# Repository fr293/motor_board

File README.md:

# stepper motor control board

This motor control board is designed to work with the [Open Flexure microscope](https://github.com/rwb27/openflexure_microscope) and connect to a Raspberry Pi.  It is based around three parallel ATTiny 841 microcontrollers running the Arduino Firmware through SpenceKonde's [ATTinyCore](https://github.com/SpenceKonde/ATTinyCore). 

Each ATTiny 841 controls a ULN2003 Darlington transistor array operating at 5V, running a 28BYJ-48 stepper motor with a 64:1 gear ratio.

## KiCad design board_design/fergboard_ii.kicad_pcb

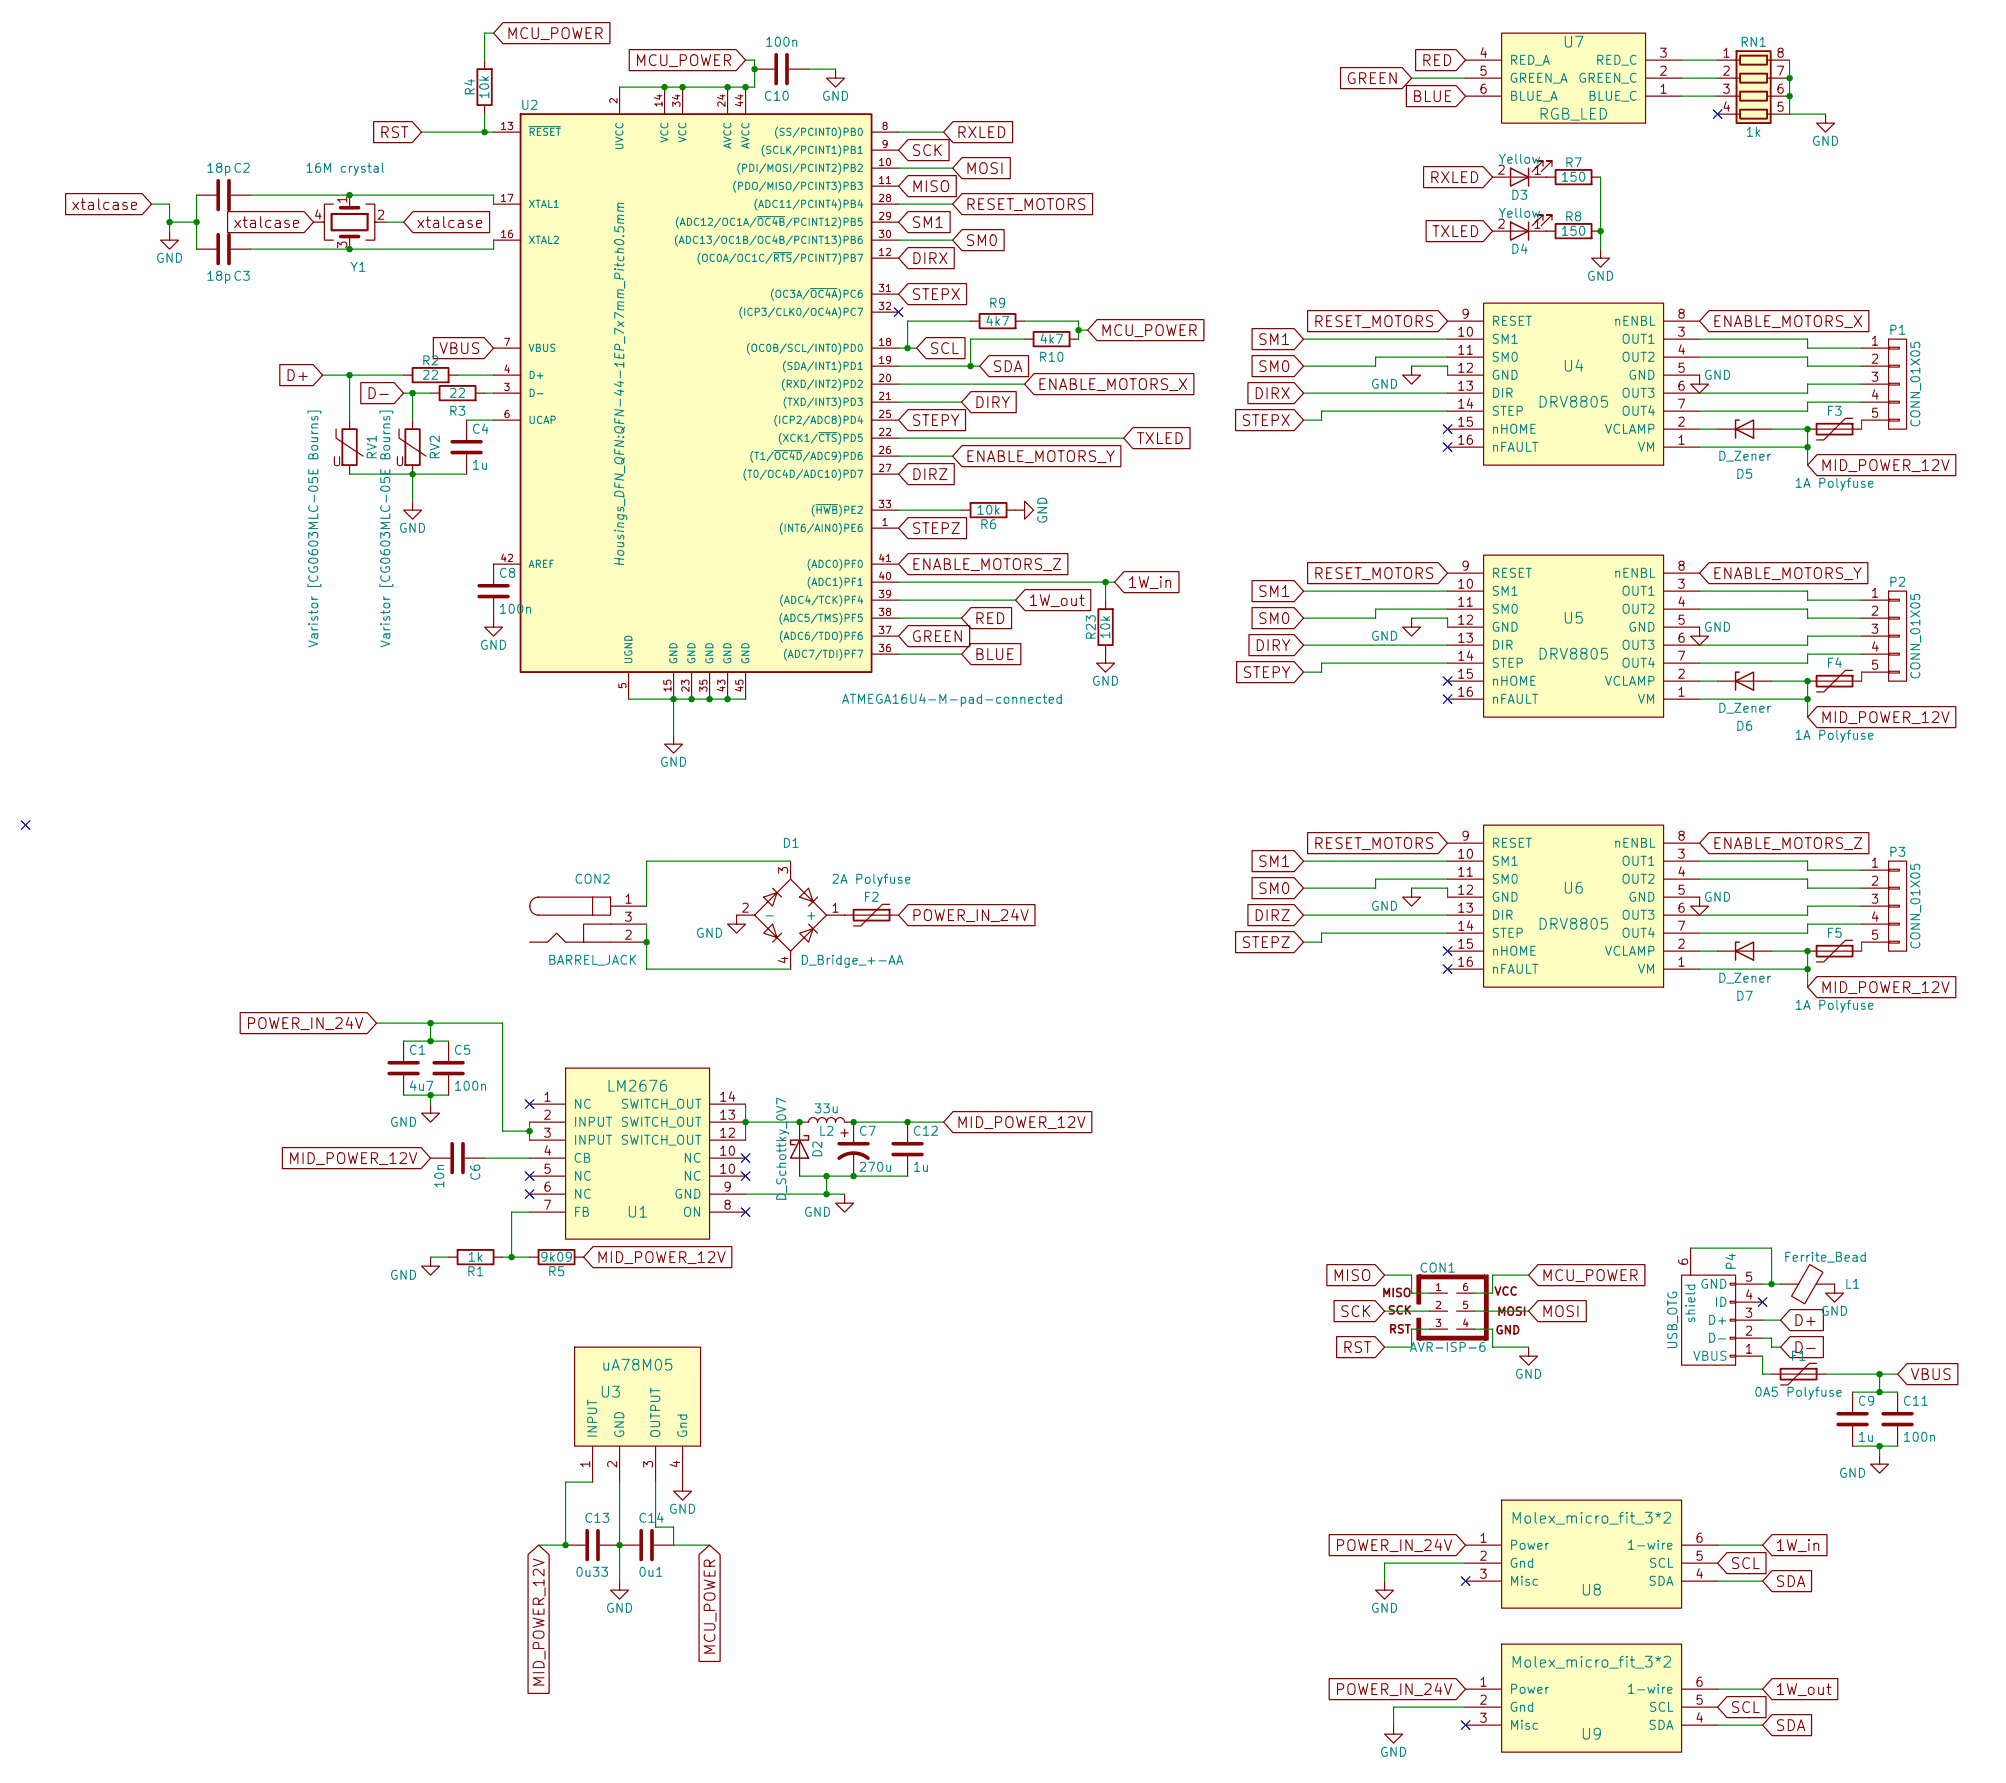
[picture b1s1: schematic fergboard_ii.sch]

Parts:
C1: 4u7; R_2816
C2, C3: 18p; C_0805
C4, C9, C12: 1u; C_0805
C5, C8, C10, C11: 100n; C_0805
C6: 10n; C_0805
C7: 270u; R_2816
C13: 0u33; C_0805
C14: 0u1; C_0805
CON1: AVR-ISP-6; SW_NKK_G1xJP
CON2: BARREL_JACK; SMD_Jack
D1: D_Bridge_+-AA; CD-HD2004
D2: D_Schottky_0V7; D_1206
D3, D4: Yellow; LED_0805
D5, D6, D7: D_Zener; D_SOD-323
F1: 0A5 Polyfuse; R_1206
F2: 2A Polyfuse; R_1206
F3, F4, F5: 1A Polyfuse; R_1206
L1: Ferrite_Bead; R_0805
L2: 33u; Choke_SMD_6.3x6.3_H3
P1, P2, P3: CONN_01X05; Molex_KK-6410-05_05x2.54mm_Straight
P4: USB_OTG; USB_Micro_B
R1: 1k; R_0805
R2, R3: 22; R_0805
R4, R6, R23: 10k; R_0805
R5: 9k09; R_0805
R7, R8: 150; R_0805
R9, R10: 4k7; R_0805
RN1: 1k; R_Array_Convex_4x0603
RV1, RV2: Varistor [CG0603MLC-05E Bourns]; R_0603
U1: LM2676
U2: ATMEGA16U4-M-pad-connected; QFN-44-1EP_7x7mm_Pitch0.5mm
U3: uA78M05; SOT-223
U4, U5, U6: DRV8805
U7: RGB_LED
U8, U9: Molex_micro_fit_3*2; molex_micro_fit_3_by_2_right_angle
Y1: 16M crystal; Crystal_SMD_3225-4pin_3.2x2.5mm

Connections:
1W_in: R23.2, U2.40 ((ADC1)PF1), U8.6 (1-wire)
1W_out: U2.39 ((ADC4/TCK)PF4), U9.6 (1-wire)
BLUE: U2.36 ((ADC7/TDI)PF7), U7.6 (BLUE_A)
D+: P4.3 (D+), R2.1, RV1.1
D-: P4.2 (D-), R3.1, RV2.1
DIRX: U2.12 ((OC0A/OC1C/~RTS~/PCINT7)PB7), U4.13 (DIR)
DIRY: U2.21 ((TXD/INT3)PD3), U5.13 (DIR)
DIRZ: U2.27 ((T0/OC4D/ADC10)PD7), U6.13 (DIR)
ENABLE_MOTORS_X: U2.20 ((RXD/INT2)PD2), U4.8 (nENBL)
ENABLE_MOTORS_Y: U2.26 ((T1/~OC4D~/ADC9)PD6), U5.8 (nENBL)
ENABLE_MOTORS_Z: U2.41 ((ADC0)PF0), U6.8 (nENBL)
GREEN: U2.37 ((ADC6/TDO)PF6), U7.5 (GREEN_A)
MCU_POWER: C10.1, C14.1, CON1.6, R4.2, R9.2, R10.2, U2.2 (UVCC), U2.14 (VCC), U2.24 (AVCC), U2.34 (VCC), U2.44 (AVCC), U3.3 (OUTPUT)
MID_POWER_12V: C6.2, C7.1, C12.1, C13.2, D5.2 (A), D6.2 (A), D7.2 (A), F3.2, F4.2, F5.2, L2.2, R5.1, U3.1 (INPUT), U4.1 (VM), U5.1 (VM), U6.1 (VM)
MISO: CON1.1, U2.11 ((PDO/MISO/PCINT3)PB3)
MOSI: CON1.5, U2.10 ((PDI/MOSI/PCINT2)PB2)
unnamed: C2.1, U2.17 (XTAL1), Y1.1
unnamed: C3.1, U2.16 (XTAL2), Y1.3
unnamed: C4.1, U2.6 (UCAP)
unnamed: C6.1, U1.4 (CB)
unnamed: C8.1, U2.42 (AREF)
unnamed: CON2.1, D1.3
unnamed: CON2.2, CON2.3, D1.4
unnamed: D1.1 (+), F2.2
unnamed: D2.1 (K), L2.1, U1.12 (SWITCH_OUT), U1.13 (SWITCH_OUT), U1.14 (SWITCH_OUT)
unnamed: D3.1 (K), R7.1
unnamed: D4.1 (K), R8.1
unnamed: D5.1 (K), U4.2 (VCLAMP)
unnamed: D6.1 (K), U5.2 (VCLAMP)
unnamed: D7.1 (K), U6.2 (VCLAMP)
unnamed: F1.2, P4.1 (VBUS)
unnamed: F3.1, P1.5
unnamed: F4.1, P2.5
unnamed: F5.1, P3.5
unnamed: L1.1, P4.5 (GND), P4.6 (shield)
unnamed: P1.1, U4.3 (OUT1)
unnamed: P1.2, U4.4 (OUT2)
unnamed: P1.3, U4.6 (OUT3)
unnamed: P1.4, U4.7 (OUT4)
unnamed: P2.1, U5.3 (OUT1)
unnamed: P2.2, U5.4 (OUT2)
unnamed: P2.3, U5.6 (OUT3)
unnamed: P2.4, U5.7 (OUT4)
unnamed: P3.1, U6.3 (OUT1)
unnamed: P3.2, U6.4 (OUT2)
unnamed: P3.3, U6.6 (OUT3)
unnamed: P3.4, U6.7 (OUT4)
unnamed: R1.1, R5.2, U1.7 (FB)
unnamed: R2.2, U2.4 (D+)
unnamed: R3.2, U2.3 (D-)
unnamed: R6.2, U2.33 ((~HWB~)PE2)
unnamed: RN1.1 (R1.1), U7.3 (RED_C)
unnamed: RN1.2 (R2.1), U7.2 (GREEN_C)
unnamed: RN1.3 (R3.1), U7.1 (BLUE_C)
POWER_IN_24V: C1.1, C5.1, F2.1, U1.2 (INPUT), U1.3 (INPUT), U8.1 (Power), U9.1 (Power)
RED: U2.38 ((ADC5/TMS)PF5), U7.4 (RED_A)
RESET_MOTORS: U2.28 ((ADC11/PCINT4)PB4), U4.9 (RESET), U5.9 (RESET), U6.9 (RESET)
RST: CON1.3, R4.1, U2.13 (~RESET~)
RXLED: D3.2 (A), U2.8 ((SS/PCINT0)PB0)
SCK: CON1.2, U2.9 ((SCLK/PCINT1)PB1)
SCL: R9.1, U2.18 ((OC0B/SCL/INT0)PD0), U8.5 (SCL), U9.5 (SCL)
SDA: R10.1, U2.19 ((SDA/INT1)PD1), U8.4 (SDA), U9.4 (SDA)
SM0: U2.30 ((ADC13/OC1B/OC4B/PCINT13)PB6), U4.11 (SM0), U5.11 (SM0), U6.11 (SM0)
SM1: U2.29 ((ADC12/OC1A/~OC4B~/PCINT12)PB5), U4.10 (SM1), U5.10 (SM1), U6.10 (SM1)
STEPX: U2.31 ((OC3A/~OC4A~)PC6), U4.14 (STEP)
STEPY: U2.25 ((ICP2/ADC8)PD4), U5.14 (STEP)
STEPZ: U2.1 ((INT6/AIN0)PE6), U6.14 (STEP)
TXLED: D4.2 (A), U2.22 ((XCK1/~CTS~)PD5)
VBUS: C9.1, C11.1, F1.1, U2.7 (VBUS)
xtalcase: C1.2, C2.2, C3.2, C4.2, C5.2, C7.2, C8.2, C9.2, C10.2, C11.2, C12.2, C13.1, C14.2, CON1.4, D1.2 (-), D2.2 (A), L1.2, R1.2, R6.1, R7.2, R8.2, R23.1, RN1.5 (R4.2), RN1.6 (R3.2), RN1.7 (R2.2), RN1.8 (R1.2), RV1.2, RV2.2, U1.9 (GND), U2.5 (UGND), U2.15 (GND), U2.23 (GND), U2.35 (GND), U2.43 (GND), U2.45 (GND), U3.2 (GND), U3.4 (Gnd), U4.5 (GND), U4.12 (GND), U5.5 (GND), U5.12 (GND), U6.5 (GND), U6.12 (GND), U8.2 (Gnd), U9.2 (Gnd), Y1.2, Y1.4

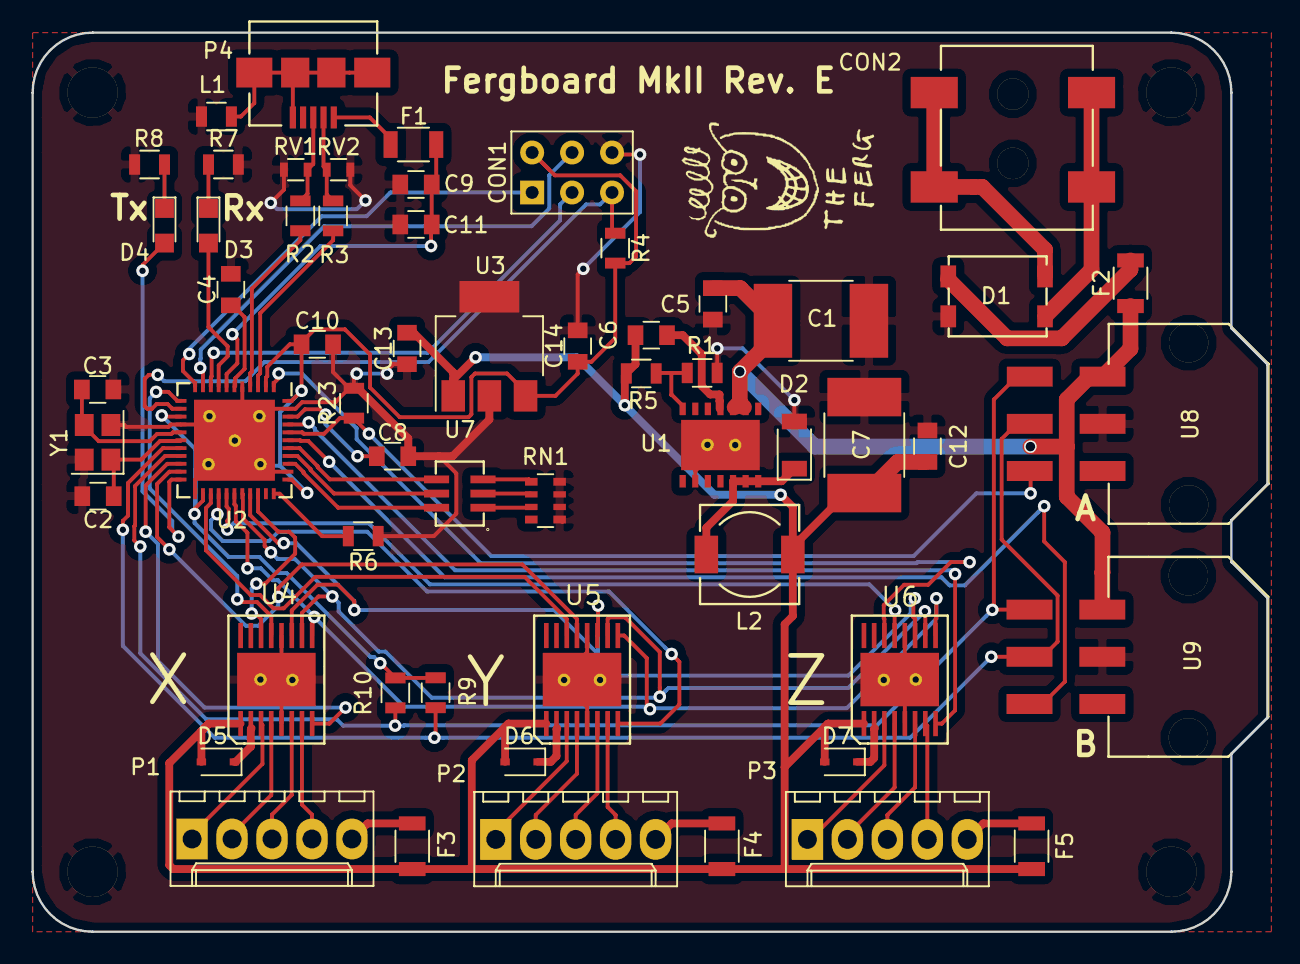
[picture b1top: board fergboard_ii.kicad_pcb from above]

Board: 2 copper layers, 78.5 x 57.2 mm, 58 parts (0 on the bottom side), 70 nets.

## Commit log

2016-05-06 Added files via upload
2016-05-18 Add files via upload
    This model is a reasonably accurate upper bound on the 28BYJ-48 – 5V Stepper Motor
2016-10-18 Added bill of materials
    I went through the eagle files and made a bill of materials in an ODF
    spreadsheet. It has generic part specifications, footprints, and part
    numbers for the Digikey catalog.
2016-10-18 updated BOM
    resolved notes, updated parts quantities, confirmed ATTiny 841
2016-10-27 SMT stencils
    added board stencils for surface mount solder application
2016-10-31 Added info about the ATTinyCore in Readme
2016-11-02 added stencil DXF, fixed BSS138 digikey part X in BOM
